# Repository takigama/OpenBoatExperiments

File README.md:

# OpenBoat

Getting back into sailing after a number of years and my electronics itch is wanting me to make an entirely open-source sailing boat computer system.

So far this is a dump of my ideas and nothing more.

# The Main Ideas

I want to dump my main ideas that i've not seen done anywhere and I think are inovative (for boats)

 - Wireless everything (esp32-c6 has wifi, bluetooth and zibgee - unfortunately aliexpress delivered my esp32-c6 to a garbage bin so i havent been able to test the zigbee bit) so everything is done over wifi with bluetooth and zigbee backups
 - Wireless charging!, the idea is to remove any form of water ingress by everything external being plastic and well sealed. The display units (4"-7" ESP32's you can get almost anywhere) would have a lithium battery on board and the "mount" would be the charger side - nothing metal need be exposed to the weather and allows you to pick up the unit - Think QI chargers, many available as arduino modules
 - The Big one - Man Over Board detection. This is the one i've been trying to get working really hard and failing with and could be done REALLY cheaply. Google and Apple "find hub"/"find my" tags. It should be easy to implement, you just have to pair from the esp32 to the tag, figure out an IRK between them and then keep track of it. Every device on the boat is based on ESP32's, so every device can track the visibility of the device. Needs to be 100% offline-able
 - Dead man autopilot - I wanted an autopilot model that could connect itself, either as a simple dead-man switch in the cockpit or some form of human detection that auto-connects the AP when no ones at the helm. This is important for the man over board detection.

# Components

## connectivity

Everything will be connected via wifi using ESP32's. There will be some form of router required (preferably something openwrt based that can handle running gpsd and mqtt). The core of eveyrthing will be mqtt. I tried to get on board with signalk, but MQTT has lot more support and being able to subscribe to different data sets is advantageous here (it doesn't appear signalK can do that).

## sensors

First thing im designing is a boat that will have an esp32 + accelerometer + gyro + magnetometer + gps... This should be easy enough to do quite cheaply (around $20 each). They'll publish all their data to gpsd and mqtt.

Second will be an AIS receiver (or two) based on dAISy or RTL-SDR

## displays

Theres quite a number of 5-10" lcd's with onboard esp32's that i'll be targetting, and they are quite cheap too. I'll probably be coding those from scratch. These will connect back to some central machine on the boat that tells them what to display. They'll be 3 buttons on each display, one for paging, one for silencing alarms and one for something else. Each display will be identified by its mac address (or some chip id) and all devices will run a single firmware that gets OTA updated from the central machine.

## central machine

Basically something that can run a web interface that will control the displays and consume information. At the moment, this might be a nanopi friendly elec with hdmi output that'll come to a normal 24" tv in the boat. Be capable of running opencpn and the web control interface (probably node as a docker container).

Hopefully the tv will be somewhere you might be able to swivel it so you can see it from the tiller/wheel.

## opencpn exporting...

it would be nice to be able to select a course in opencpn then be able to export details back to displays.. For eg, if you're off-track, something similar to a aircraft nav display (HSI) would be interesting... can show both deviation from heading and deviation from line at the same time.

## other sensors.

a 3d printed wind speed/direction sensor would be an interesting addition.

There is one diy depth sounder, but we'll see, its not hugely encouraging.

Most boats already have some form of speed indicator, reading it from an ESP32 should be pretty trivial.. The rest of the information about speeds and directions should be able to be gotten from gps and wind speed/direciton sensor.

Now, heres where things can get interesting, and also why I want to combine everything into a single cohesive brain. The sensors will have tilt/gyro/accel/pressure, etc and gps, combining all of this is going to be a fun little math problem, but should result in extremely acurate speed. GPS are impressively accurate for speed (nothing really comes close), but there are reasons why it may not be in alot of cases directly accurate on a boat. However, combining all the gyro/accell/tilt data should bring the accuracy much close. Not looking forward to doing that calculus, though hopefully someone already has. There is a part of them that realises theres no real need for that kind of accurace on a sailboat (shhh, i dont care).

## types of displays

HSI like NAV on an airplane would be very cool

Compass that shows boat heading (i.e. where the front is pointed) and any deviation for the boat travel (i.e. are we sidling) - plus other pointers to things like closest land heading, other boats, etc.

Small vector map dislpay would be nice, but may be hard to get vector maps from anywhere that is useful, also showing any details about other boats from AIS.

Some form of radio sensor

volts/amps, etc

Autopilot stuff...

## Autopilot....

There's already fenix for open AP, though i had an idea for a different control mechism that doesnt use a linear actuator.

## The wearable...

So one other thing I'd love is a wrist wearable 7" display similar to the other displays.

## other projects...

openplotter and fenix are interesting and possibly useful for some of the stuff, but i dont like RPI's for this kind of thing, the lack of on-board storage and everything on the SD card i've had to many issues with it in other mobile things or anywhere thats might be needing to be a bit hardened.

## Power control.

One other facet I want to include in all components it the ability for the ESP's to "disable" stuff (i.e. turn off the GY-86, gps or several of the displays). this is useful when anchored cause you really only need one gps to be sending data with no real displays and if you get a sudden movement, power everything back up again.

## AI Detection

Another interesting concept to explore is frigate. Frigate is an NVR thats existed for a long time but uses the Coral TPU (and other inference capable devices) with tensor flow to do image recog (mine at home has been trained to recognise me, my partner and both our dogs very accurately). A "fork" of frigate that was designed to do image recognition would be very interesting on boat.... the sort of thing im talking about it:
 - water navigation marks
 - other boats
 - people overboard
 - land and other water marks.
... and other things?

AI could also be extended to the autopilot intreesting ways when combined with all the sensors available.

# Building the firmware

Every ESP32 firmware here builds the same way - PlatformIO inside one Docker image, driven by one script (run it from Linux/WSL):

```
build/build.sh --list                # what can be built
build/build.sh EngineControl         # a project (all of its firmware)
build/build.sh ESP32Seatalk          # or one firmware
build/build.sh all
```

The result is in `build/firmware/` as `TOBE-<name>-v<version>.bin` (TOBE = takigama open boat experiments). The code the projects share - serial
command line, web pages and WiFi setup mode, over-the-air updates, the ESP-NOW secret - lives in [`lib/`](lib/README.md); how the build, the
registry of firmware (`build/projects.json`) and releases work is in [`build/README.md`](build/README.md). (SignalKPaperDisplay is a Go program for the
Kindles and has its own build.)

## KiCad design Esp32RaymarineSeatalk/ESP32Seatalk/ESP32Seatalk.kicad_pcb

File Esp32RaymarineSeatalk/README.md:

A really simple board for connecting an ESP32-C3-OLED board to seatalk as an in-path or end-of-path device.

Also has support for CAN BUS (for NEMA2000) and UART extension (which will be useful for the project revolving around using google tags as MOB tokens)

Firmware (SeaTalk/CAN/MQTT/SignalK bridge) lives in [`PlatformIO/ESP32Seatalk`](PlatformIO/ESP32Seatalk/README.md) - see that README for the MQTT topic mapping, web UI, and everything else.

## The built board

> **The board in these photos is version 1.** A version 2 is almost ready; this section will be updated when it is.

A bare board and the same board built up: an ESP32-C3 module with its small OLED sits on the carrier board
(its small display shows what the firmware is doing); the SeaTalk connectors are on the two sides, and the
voltage regulator (U1) with its capacitors, the BSS138 level shifter (Q1) for the one-wire SeaTalk line and
two resistors (R1, R2) are on the back.

| Bare PCB, component side | Bare PCB, back |
|---|---|
|  |  |

| Built: front | Built: back |
|---|---|
|  |  |

The two white 3-pin connectors (J1 and J2, the red / yellow / black leads) are SeaTalk: +12 V, data and ground.
The board takes its power from the bus, so it sits in the path of the bus or at its end. The 5-way header at the
top (J4) is where a plug-in CAN transceiver module goes, and the transceiver's CANH / CANL leave on connector
J3; neither is fitted in these photos.

### With its cables

The board with its two SeaTalk lead cables (ferrite sleeves, round screw-lock connectors), and **no NMEA 2000
transceiver fitted**: SeaTalk only.

### Driving a real instrument

The board connected to a Raymarine **ST60+ Wind** (Autohelm series) instrument on a bench SeaTalk bus. The
firmware's demo mode sends three fixed values - speed through water, apparent wind angle and apparent wind
speed - and the instrument works out the true wind and the VMG itself. SeaTalk counts the wind angle 0-360 deg
clockwise from the bow, so a wind 60 deg off the port bow is sent as 300 deg.

| Photo | Speed through water | Apparent wind angle sent | Apparent wind speed | The instrument shows |
|---|---|---|---|---|
| APP mode | 10 kn | **315 deg** (45 deg to port) | 10 kn | apparent wind speed **10.0 kts**, needle 45 deg to port |
| TRUE mode | 10 kn | **300 deg** (60 deg to port) | 10 kn | true wind speed **10.0 kts**, true wind angle **120 deg** to port |
| VMG mode | 10 kn | **300 deg** (60 deg to port) | 10 kn | VMG **-5.0 kts**, needle 120 deg to port |

| ST60+ in APP mode | in TRUE mode | in VMG mode |
|---|---|---|
|  |  |  |
| 45 deg to port, 10.0 kts | 120 deg to port, 10.0 kts | VMG -5.0 kts |

The instrument's numbers agree with the vector calculation. For the 60 deg photos (TRUE and VMG): true wind
angle atan2(10 sin 60, 10 cos 60 - 10) = **120 deg**, still on the port side, true wind speed
sqrt(10^2 + 10^2 - 2 x 10 x 10 x cos 60) = **10 kn**, and VMG to the wind = STW x cos(TWA) = 10 x cos 120 =
**-5.0 kn** (negative: making progress away from the wind). The APP photo was taken at a different angle, so it
only shows the apparent wind - for reference, 45 deg would have given a true wind angle of 112.5 deg, a true
wind speed of 7.7 kn and a VMG of -3.8 kn.

The needle sitting on the red (port) side of the dial for sent angles of 300 and 315 deg is also a check on the
firmware's encoding of the wind angle: high byte first, over the full 0-360 deg range.

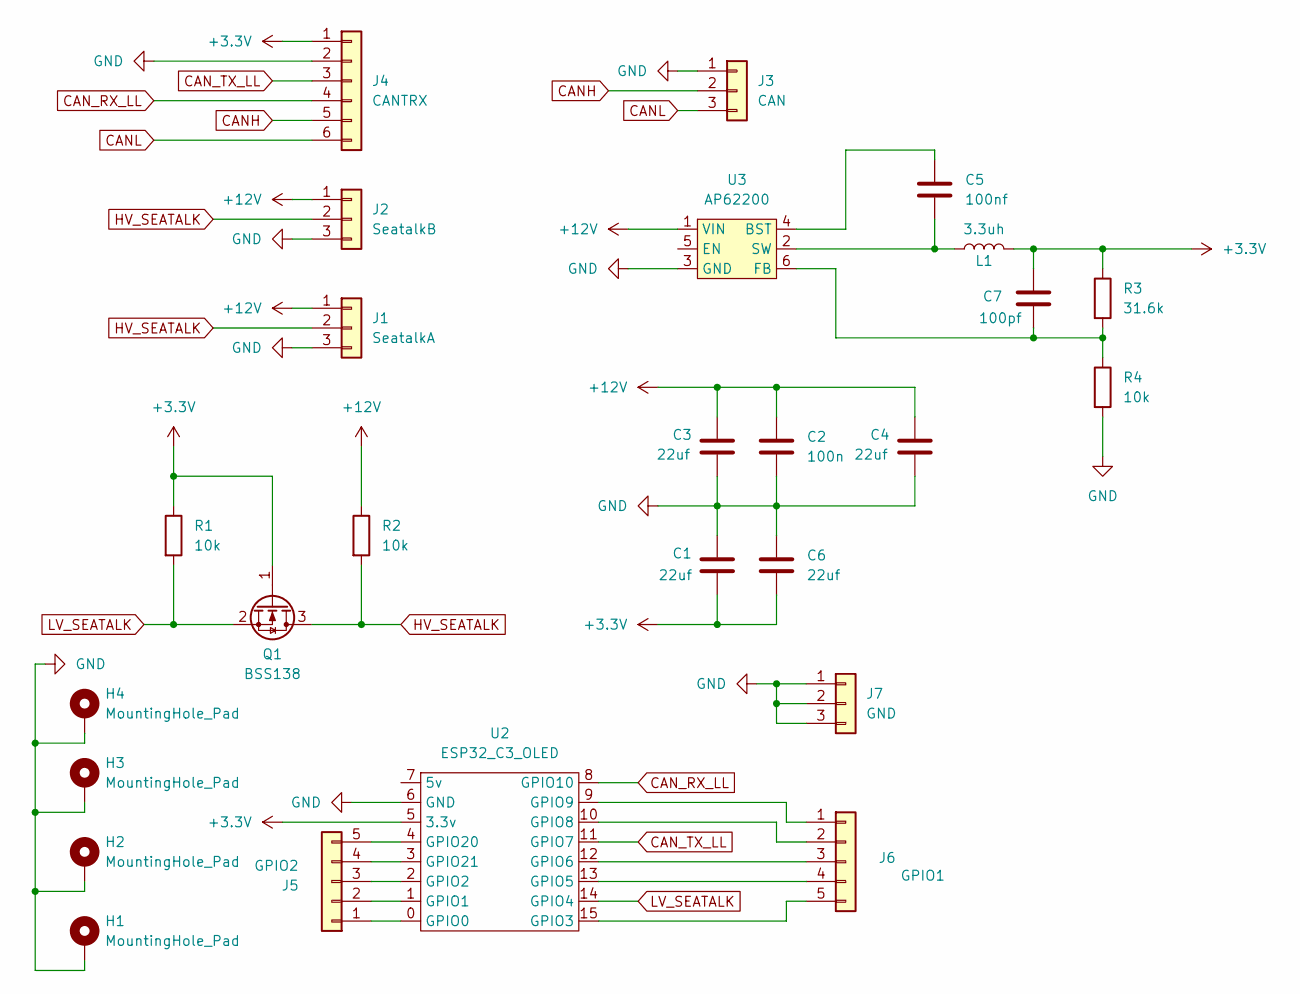
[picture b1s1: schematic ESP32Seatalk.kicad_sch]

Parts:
C1, C3, C4, C6: 22uf; C_0805_2012Metric_Pad1.18x1.45mm_HandSolder
C2: 100n; C_0805_2012Metric_Pad1.18x1.45mm_HandSolder
C5: 100nf; C_0805_2012Metric_Pad1.18x1.45mm_HandSolder
C7: 100pf; C_0805_2012Metric_Pad1.18x1.45mm_HandSolder
H1, H2, H3, H4: MountingHole_Pad; MountingHole_2.2mm_M2_ISO7380_Pad
J1: SeatalkA; PinHeader_1x03_P2.54mm_Vertical
J2: SeatalkB; PinHeader_1x03_P2.54mm_Vertical
J3: CAN; PinHeader_1x03_P2.54mm_Vertical
J4: CANTRX; PinHeader_1x06_P2.54mm_Vertical
J5: GPIO2; PinHeader_1x05_P2.54mm_Vertical
J6: GPIO1; PinHeader_1x05_P2.54mm_Vertical
J7: GND; PinHeader_1x03_P2.54mm_Vertical
L1: 3.3uh; L_Cyntec_VCHA042A-MS6
Q1: BSS138; SOT-23
R1, R2, R4: 10k; R_0805_2012Metric_Pad1.20x1.40mm_HandSolder
R3: 31.6k; R_0805_2012Metric_Pad1.20x1.40mm_HandSolder
U2: ESP32_C3_OLED; ESP-32C-OLED
U3: AP62200; SOT-563

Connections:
+3.3V: C1.2, C6.2, C7.1, J4.1, L1.2, Q1.1 (G), R1.1, R3.1, U2.5 (3.3v)
+12V: C2.1, C3.1, C4.1, J1.1, J2.1, R2.1, U3.1 (VIN)
CANH: J3.2, J4.5
CANL: J3.3, J4.6
CAN_RX_LL: J4.4, U2.8 (GPIO10)
CAN_TX_LL: J4.3, U2.11 (GPIO7)
GND: C1.1, C2.2, C3.2, C4.2, C6.1, H1.1, H2.1, H3.1, H4.1, J1.3, J2.3, J3.1, J4.2, J7.1, J7.2, J7.3, R4.2, U2.6 (GND), U3.3 (GND)
HV_SEATALK: J1.2, J2.2, Q1.3 (D), R2.2
LV_SEATALK: Q1.2 (S), R1.2, U2.14 (GPIO4)
unnamed: J5.1, U2.0 (GPIO0)
unnamed: J5.2, U2.1 (GPIO1)
unnamed: J5.3, U2.2 (GPIO2)
unnamed: J5.4, U2.3 (GPIO21)
unnamed: J5.5, U2.4 (GPIO20)
unnamed: J6.1, U2.9 (GPIO9)
unnamed: J6.2, U2.10 (GPIO8)
unnamed: J6.3, U2.12 (GPIO6)
unnamed: J6.4, U2.13 (GPIO5)
unnamed: J6.5, U2.15 (GPIO3)
unnamed: C5.1, U3.4 (BST)
unnamed: C7.2, R3.2, R4.1, U3.6 (FB)
unnamed: C5.2, L1.1, U3.2 (SW)

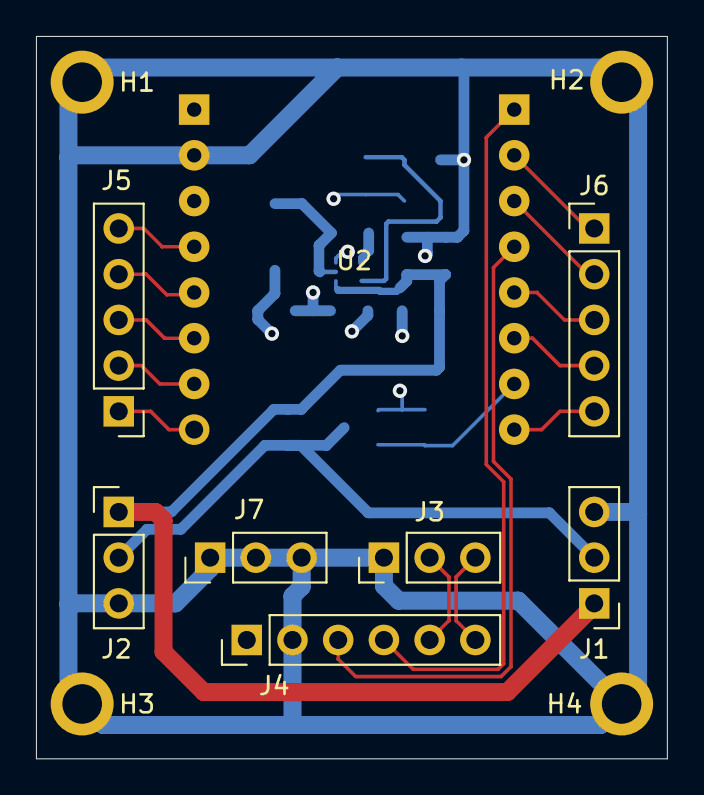
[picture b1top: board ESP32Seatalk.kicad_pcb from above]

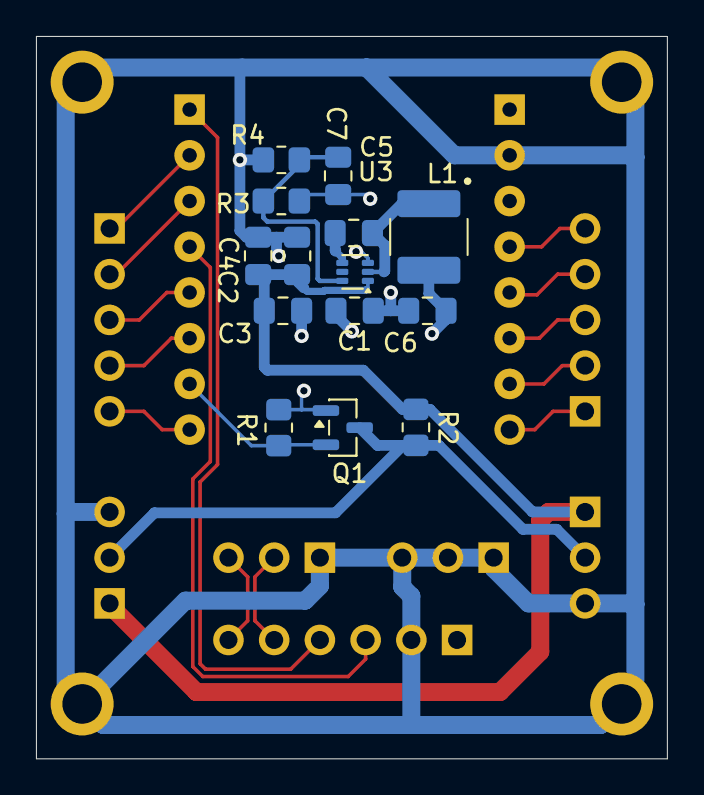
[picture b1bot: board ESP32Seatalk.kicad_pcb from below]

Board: 4 copper layers, 35.1 x 40.1 mm, 26 parts (14 on the bottom side), 22 nets.

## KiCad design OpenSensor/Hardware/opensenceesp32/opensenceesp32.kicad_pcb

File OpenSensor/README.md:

# Open sensor

## Progress!

The first version of the board has been printed and put together and is working well.

## Goal

10-30v input (there are a tonne of options here). Would may be worth doing 10-30v -> 5v as a buck then 5v -> 3.3v as an LDO for noise rejection.

esp32 (unspecific yet) connected to a gy-87 (MPU6050 HMC5883L BMP180) covering
 - Acceleration
 - gyro
 - magnetometer
 - pressure
 - temperature

And a quectel L80 GPS - i've had alot really good success with these, they are a supprisingly capable GPS that is heavily underrated. Mostly been used for timing in my world, but against a ublox 6 or MTK3339, the L80 is definitely supperiour is terms of stability. ublox is more configurable, but the only real parameter that ever really matter was delay propogation for the pps line and that has no purpose here (though the l80 does support it). The ublox has more configuartion around the sentences that it can send, but the L80 has enough configurability in its sentences to be good. Really wish they hadnt discontinued them.

## Updates

- 0.1 -- this version is working, but its not ideal. I put the sensors on their own i2c bus and the display uses a different i2c bus. Being a esp32-c3 chip it does only have a single i2c hardware bus and so the next version moves all the i2c stuff onto a single bus and adds a daylight sensor, driving the display in software i2c and the rest in hardware i2c makes it sloooowww. The code works fine and does what i wanted but is quite redumentry so far.

## ToDo

- autodetect/enable/disable devices on i2c bus
- add a web interface for config
- add signalk and nmea 2000 outputs
- trying to device if i want to move to the esp32-c6-lcd, it has so many advantages

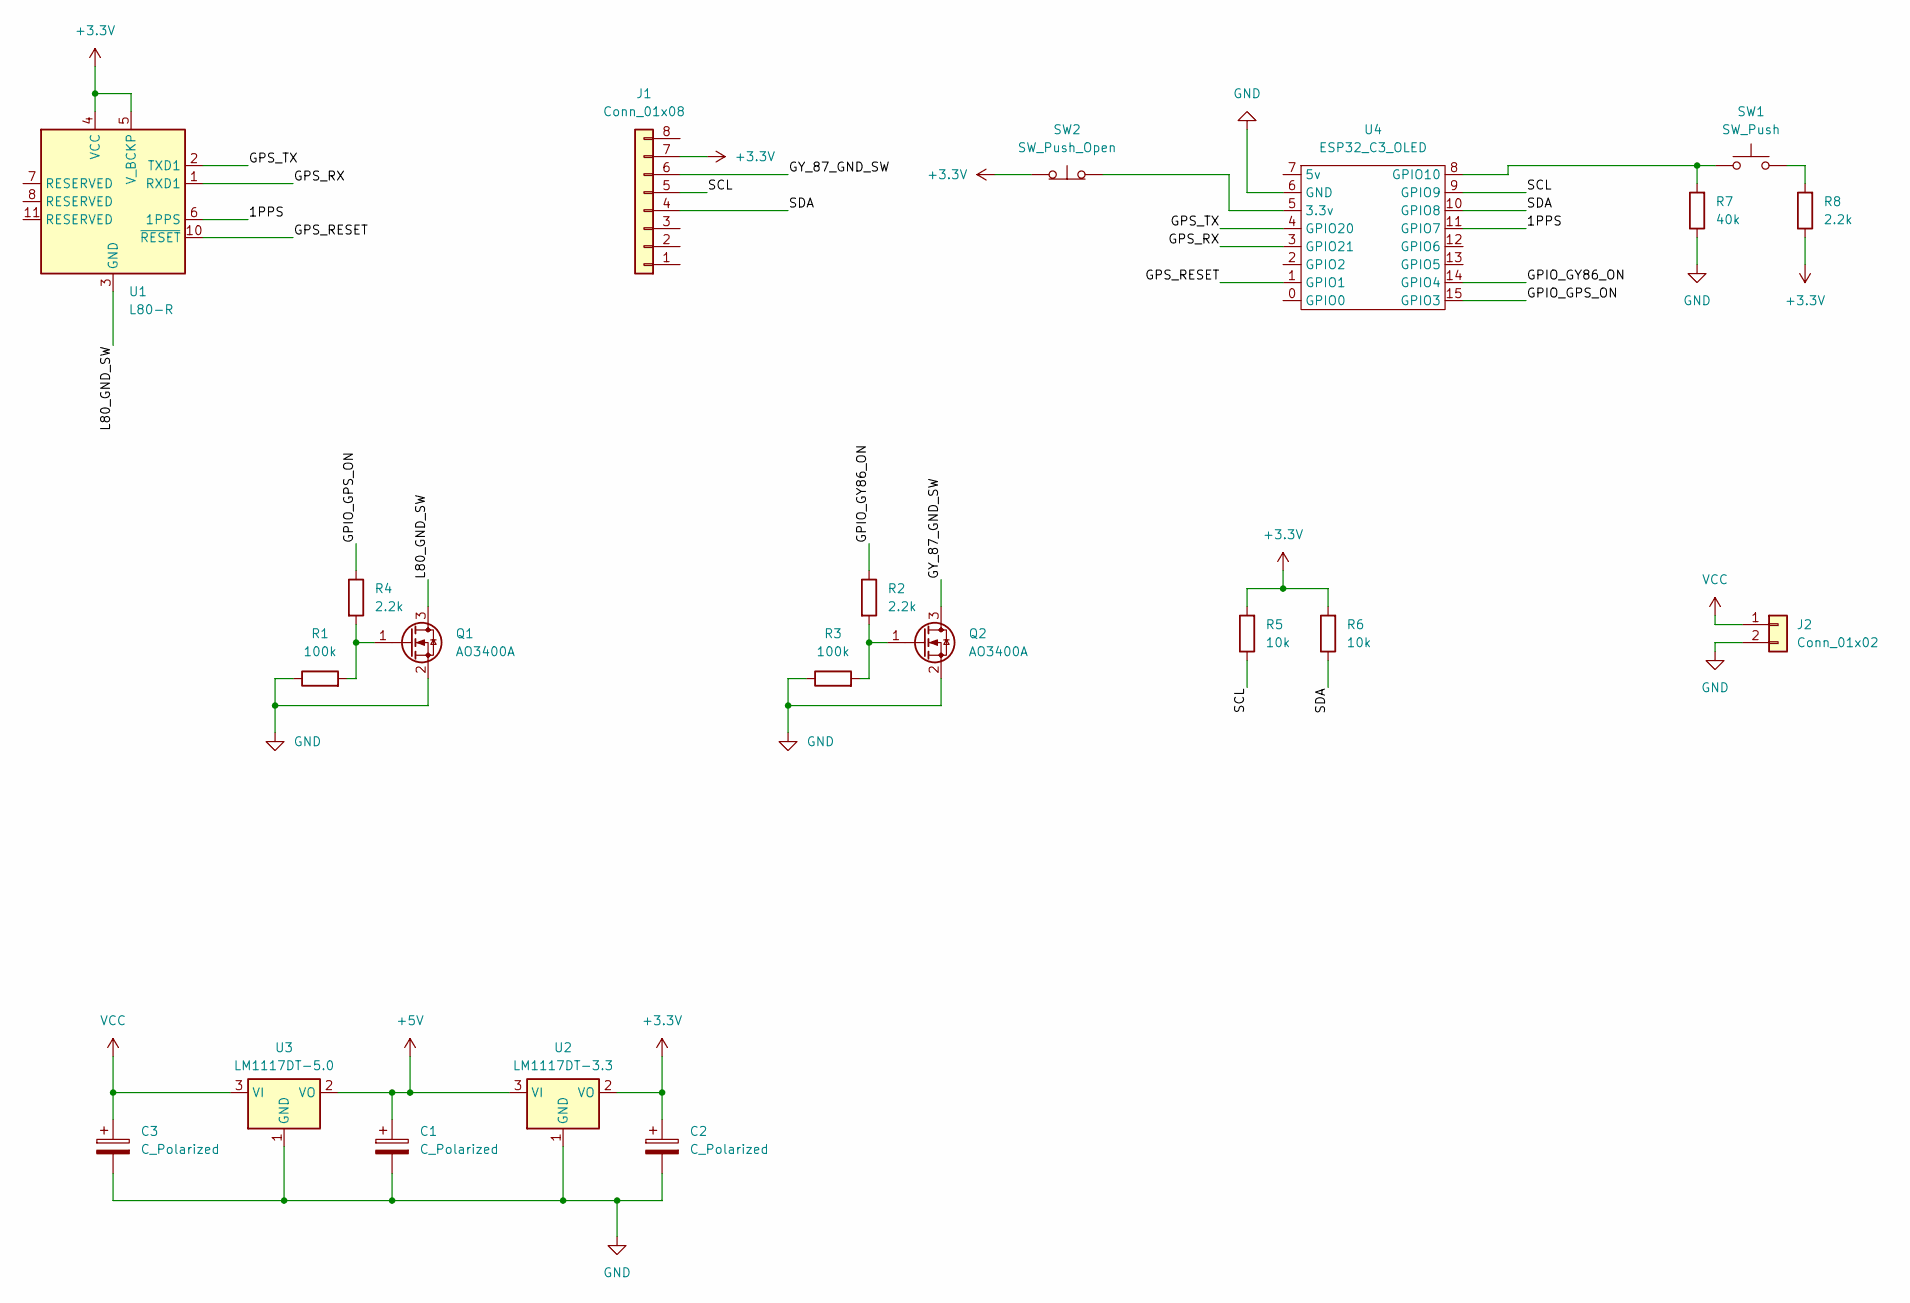
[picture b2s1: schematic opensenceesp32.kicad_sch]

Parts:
C1, C2, C3: C_Polarized; CP_EIA-3216-18_Kemet-A_HandSolder
J1: Conn_01x08; PinHeader_1x08_P2.54mm_Vertical
J2: Conn_01x02; PinSocket_1x02_P2.54mm_Vertical
Q1, Q2: AO3400A; SOT-23
R1, R3: 100k; R_1206_3216Metric_Pad1.30x1.75mm_HandSolder
R2, R4, R8: 2.2k; R_1206_3216Metric_Pad1.30x1.75mm_HandSolder
R5, R6: 10k; R_1206_3216Metric_Pad1.30x1.75mm_HandSolder
R7: 40k; R_1206_3216Metric_Pad1.30x1.75mm_HandSolder
SW1: SW_Push; PinSocket_1x02_P2.54mm_Vertical
SW2: SW_Push_Open; PinSocket_1x02_P2.54mm_Vertical
U1: L80-R; Quectel_L80-R
U2: LM1117DT-3.3; SOT-223-3_TabPin2
U3: LM1117DT-5.0; SOT-223-3_TabPin2
U4: ESP32_C3_OLED; ESP-32C-OLED

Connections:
+3.3V: C2.1, J1.7, R5.2, R6.2, R8.1, SW2.1 (A), U1.4 (VCC), U1.5 (V_BCKP), U2.2 (VO)
+5V: C1.1, U2.3 (VI), U3.2 (VO)
/1PPS: U1.6 (1PPS), U4.11 (GPIO7)
/GPIO_GPS_ON: R4.1, U4.15 (GPIO3)
/GPIO_GY86_ON: R2.1, U4.14 (GPIO4)
/GPS_RESET: U1.10 (~RESET), U4.1 (GPIO1)
/GPS_RX: U1.1 (RXD1), U4.3 (GPIO21)
/GPS_TX: U1.2 (TXD1), U4.4 (GPIO20)
/GY_87_GND_SW: J1.6, Q2.3 (D)
/L80_GND_SW: Q1.3 (D), U1.3 (GND), U1.12 (GND)
/SCL: J1.5, R5.1, U4.9 (GPIO9)
/SDA: J1.4, R6.1, U4.10 (GPIO8)
GND: C1.2, C2.2, C3.2, J2.2, Q1.2 (S), Q2.2 (S), R1.1, R3.1, R7.1, U2.1 (GND), U3.1 (GND), U4.6 (GND)
unnamed: Q1.1 (G), R1.2, R4.2
unnamed: Q2.1 (G), R2.2, R3.2
unnamed: R8.2, SW1.2
unnamed: SW2.2 (B), U4.5 (3.3v)
unnamed: R7.2, SW1.1, U4.8 (GPIO10)
VCC: C3.1, J2.1, U3.3 (VI)

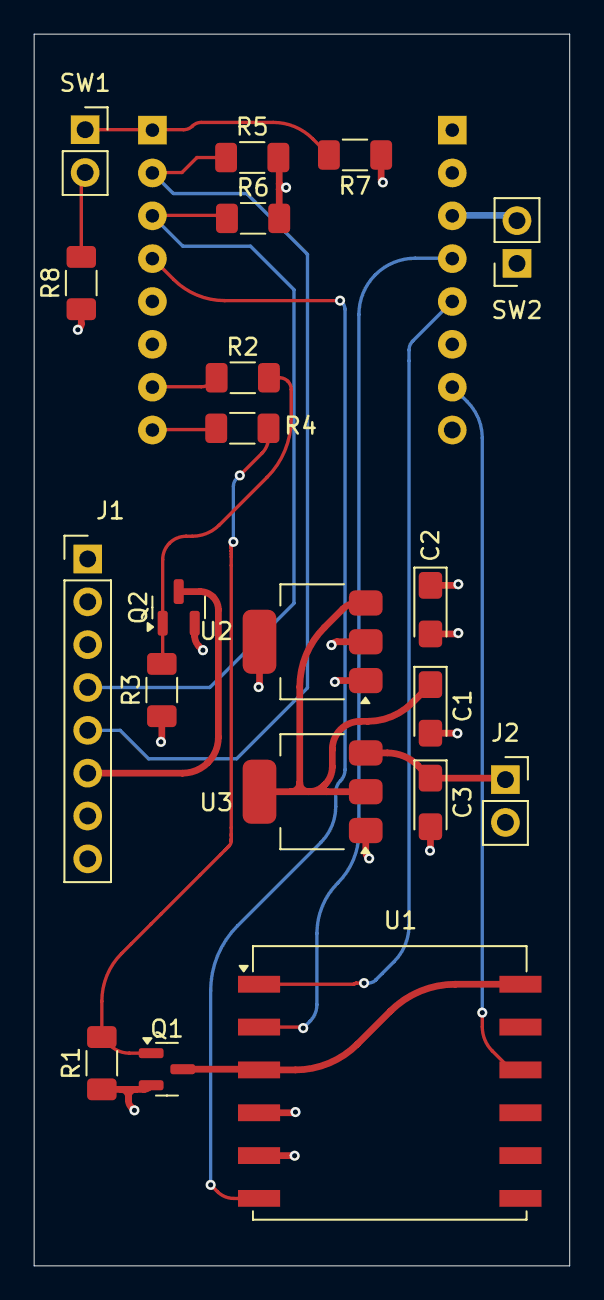
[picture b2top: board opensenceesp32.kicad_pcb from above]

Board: 4 copper layers, 31.8 x 73.0 mm, 21 parts (1 on the bottom side), 19 nets.

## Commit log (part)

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2025-09-03 initial readme
2025-09-03 opensense structure
2025-09-03 power...
2025-09-03 readme updates
2025-09-13 Added the open sensor board
2025-09-14 First draft of board
2025-09-19 components
2025-09-22 gerber
2025-12-02 off to the fab for you
2026-01-30 First printed version
2026-01-30 Updated README with photos
2026-01-31 Source for pio
2026-02-01 initial setup of code for opensensor
2026-02-04 Add the standalone hub
2026-02-25 first printed
2026-02-26 moving to 0.2 for change in pins and adding daylight sensor
2026-03-03 musings on esp32-c6
2026-03-23 idea dump
